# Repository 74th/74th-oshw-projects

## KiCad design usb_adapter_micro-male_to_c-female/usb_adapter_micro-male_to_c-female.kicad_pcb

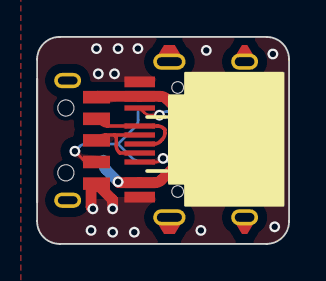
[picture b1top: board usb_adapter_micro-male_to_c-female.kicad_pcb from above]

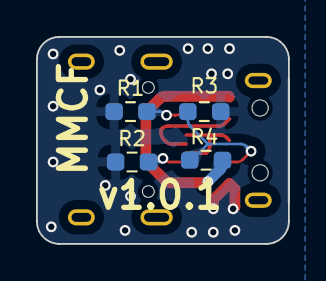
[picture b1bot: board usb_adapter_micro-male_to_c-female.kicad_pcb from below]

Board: 2 copper layers, 14.0 x 11.5 mm, 6 parts (4 on the bottom side), 7 nets.

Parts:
J2: USB2.0-C_SMT; Connector_USB-C-Receptacle_SMT_12-Pin_Simple
J3: USB_B_Micro; Connector_USB-Micro-Plug_SMD
R1, R2: 56k; Register_0603_1608
R3, R4: 10(NC); Register_0603_1608

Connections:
GND: J2.4 (GND), J3.5 (GND), R1.2, R2.2, R3.2
unnamed: J2.5 (CC1), R2.1
unnamed: J2.6 (CC2), R1.1
unnamed: J2.3 (D+), J3.2 (D-)
unnamed: J2.2 (D-), J3.3 (D+)
unnamed: J2.1 (VBUS), J3.1 (VBUS), R4.1
unnamed: J3.4 (ID), R3.1, R4.2

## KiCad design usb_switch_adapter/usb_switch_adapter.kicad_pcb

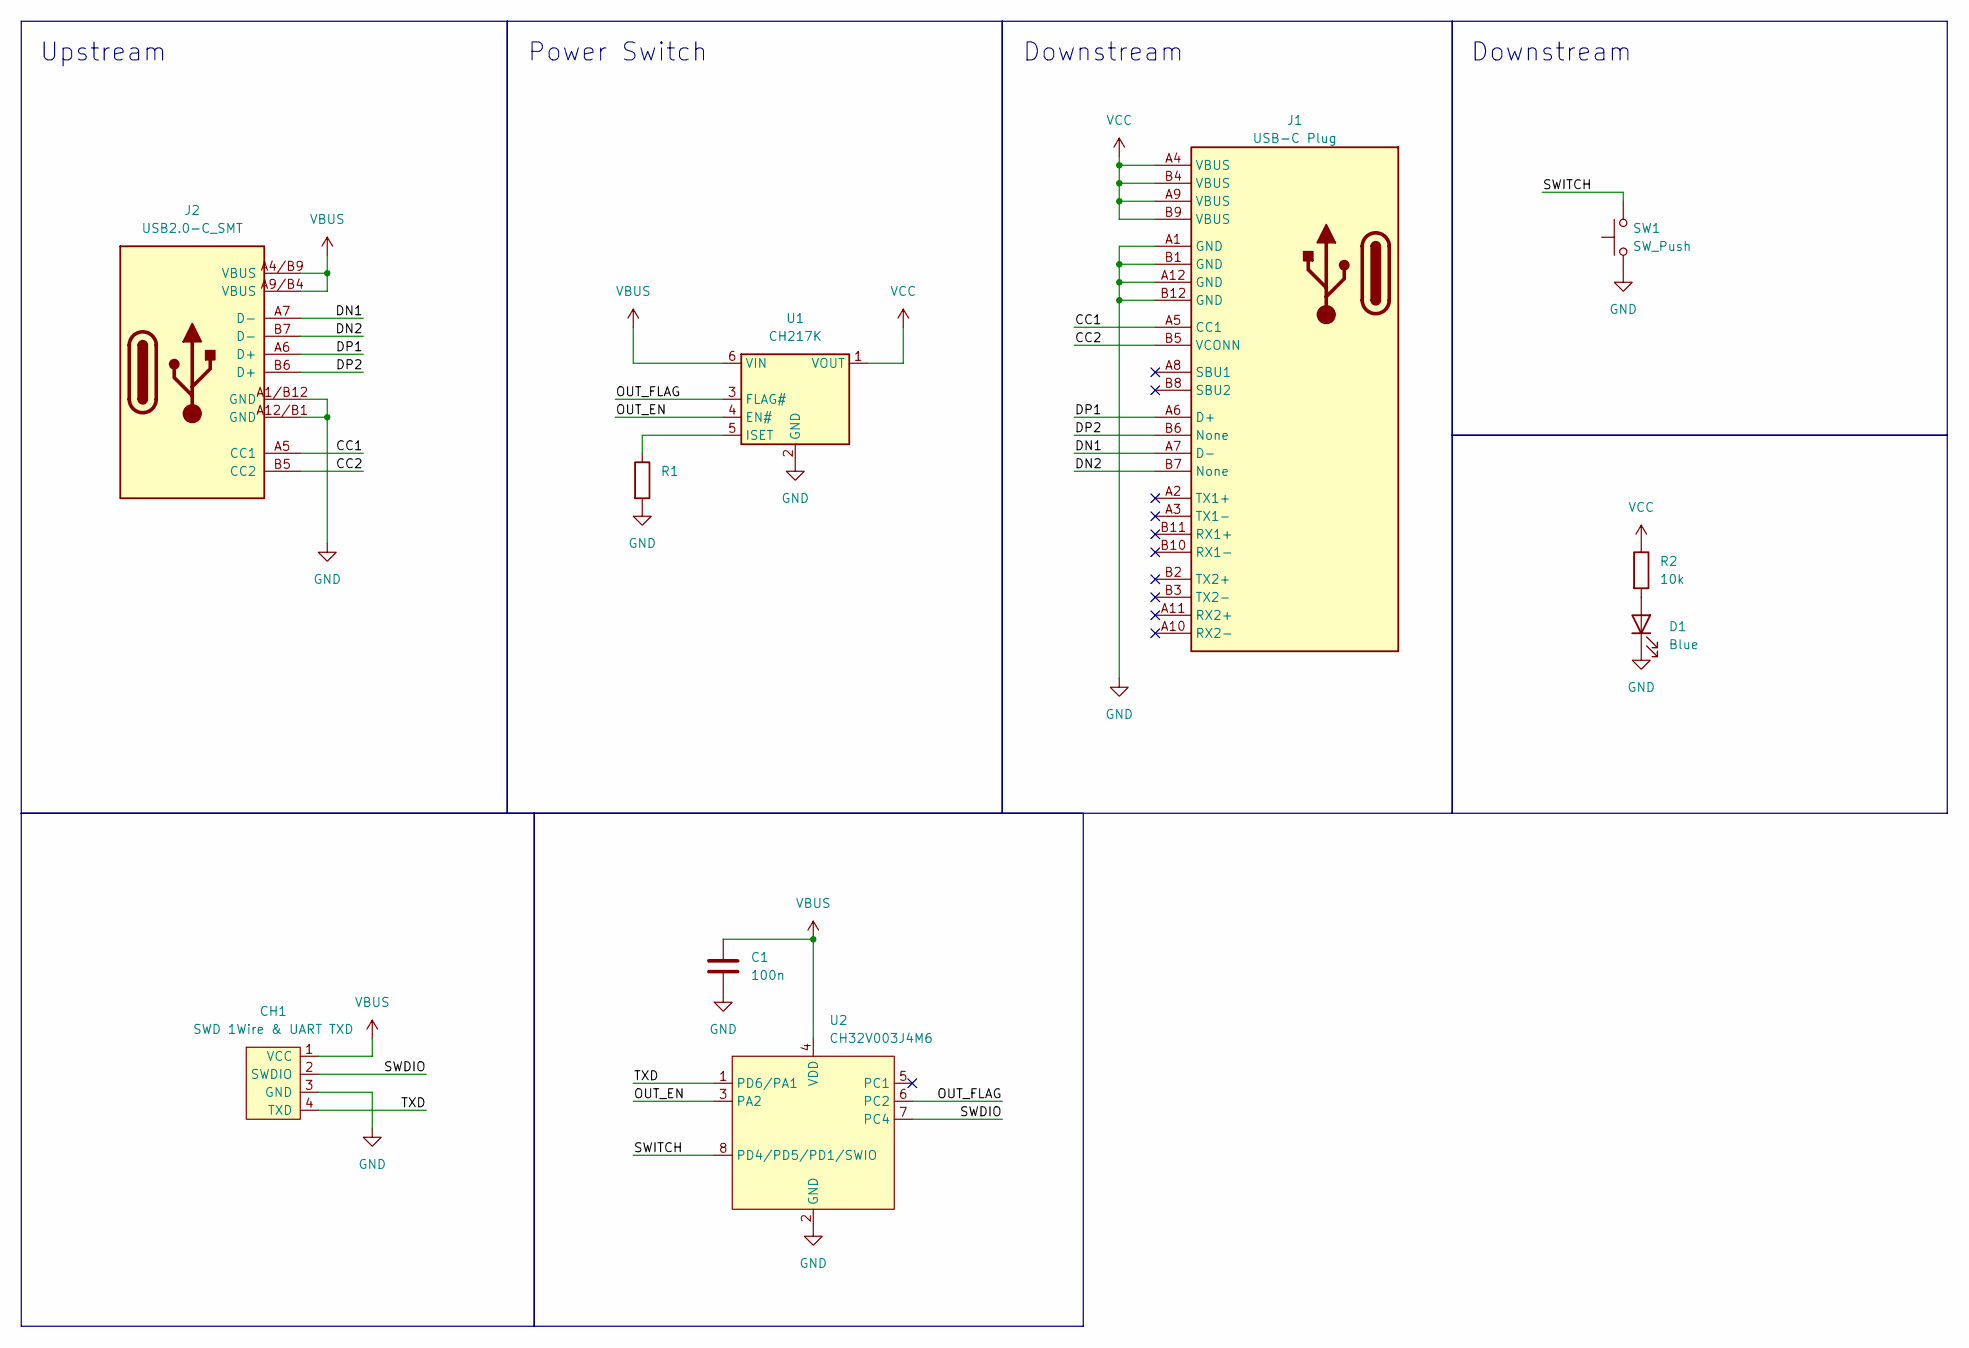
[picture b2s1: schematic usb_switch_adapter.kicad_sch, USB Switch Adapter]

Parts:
C1: 100n; Capacitor_0603_1608
CH1: SWD 1Wire & UART TXD; PinOut_Pin_4
D1: Blue; LED_BACK_0805_2012
J1: USB-C Plug; Connector_USB-C-Plug_24-Pin
J2: USB2.0-C_SMT; Connector_USB-C-Receptacle_SMT_12-Pin_MidMount
R1: 56k; Register_0603_1608
R2: 10k; Register_0603_1608
SW1: SW_Push; Switch_MXChoc_1.0u
U1: CH217K; Package_SOT-23-6
U2: CH32V003J4M6; Package_SOIC-8_3.9x4.9mm_P1.27mm

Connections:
/CC1: J1.A5 (CC1), J2.A5 (CC1)
/CC2: J1.B5 (VCONN), J2.B5 (CC2)
/DN1: J1.A7 (D-), J2.A7 (D-)
/DN2: J1.B7 (None), J2.B7 (D-)
/DP1: J1.A6 (D+), J2.A6 (D+)
/DP2: J1.B6 (None), J2.B6 (D+)
/OUT_EN: U1.4 (EN#), U2.3 (PA2)
/OUT_FLAG: U1.3 (FLAG#), U2.6 (PC2)
/SWDIO: CH1.2 (SWDIO), U2.7 (PC4)
/SWITCH: SW1.2, U2.8 (PD4/PD5/PD1/SWIO)
/TXD: CH1.4 (TXD), U2.1 (PD6/PA1)
GND: C1.2, CH1.3 (GND), D1.1 (K), J1.A1 (GND), J1.A12 (GND), J1.B1 (GND), J1.B12 (GND), J2.A1/B12 (GND), J2.A12/B1 (GND), R1.2, SW1.1, U1.2 (GND), U2.2 (GND)
unnamed: D1.2 (A), R2.2
unnamed: R1.1, U1.5 (ISET)
VBUS: C1.1, CH1.1 (VCC), J2.A4/B9 (VBUS), J2.A9/B4 (VBUS), U1.6 (VIN), U2.4 (VDD)
VCC: J1.A4 (VBUS), J1.A9 (VBUS), J1.B4 (VBUS), J1.B9 (VBUS), R2.1, U1.1 (VOUT)

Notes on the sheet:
Power Switch
Downstream
Upstream

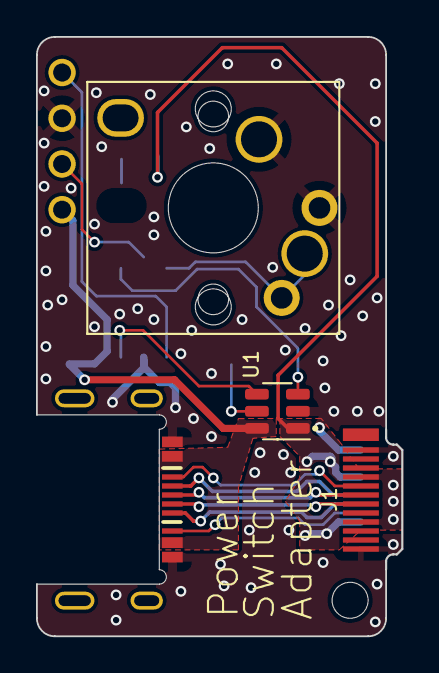
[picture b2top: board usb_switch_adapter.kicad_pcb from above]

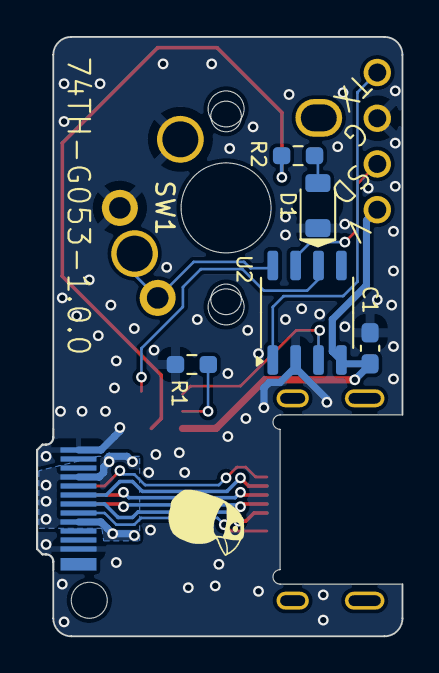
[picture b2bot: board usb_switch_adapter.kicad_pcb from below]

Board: 2 copper layers, 20.3 x 33.3 mm, 12 parts (6 on the bottom side), 16 nets.

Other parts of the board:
M2: Hole_M2_2.0
MISC-ICON: LOGO; Logo_74th_5mm
